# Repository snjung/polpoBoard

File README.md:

# polpoBoard

## Introduction
This repository compiles code and documentation for an electronic scoreboard. It has been successfully operated for several years and was continuously updated and improved.
The idea and inspiration comes from the awesome folks from Westbury on Severn Cricket Club
You can find their blog with tons of useful information on the project at https://buildyourownscoreboard.wordpress.com/

The main idea is to have a Raspberry Pi acting as a web-server and providing control of the scoreboard via a simple webpage to connected devices. The Raspberry Pi will transmit the data to be shown on the scoreboard to an arduino board via serial interface. The Arduino will then control the hardware. Currently this includes
- Custom Build 7-segment elements to show goals and time left of the current game
- A 12V car horn used for signaling end of game / half-time
- Display-Panels build of 8x8 dot-matrix LED elements to show the names of the teams

### Hardware

#### 7-Segment Elements

The 7-Segment elements are custom build and consist of 12V-LED stripes or bars. 

### Control Scheme

To control the high number of LED elements by a single microcontroller (4 x 2digits x 7 LED elements), the schematics uses shift registers for multiplexing.
Some great explanation of the functionality for a shift register can be found at https://www.mikrocontroller.net/articles/AVR-Tutorial:_Schieberegister
Each shift register provides 8 output channels and can be used to control one individual digit of the scoreboard. All shift registers can be cascaded (serial_out connected to serial_in of the next IC) and controlled via one single data pin.
The electrical signals we need are:
- **Serial Data**: Sequence of bit-values indicating if a specific output channel should be enabled/disabled. Due to the shifting, the first bit send to the shift registers will end up to be the last channel of the last register in the chain.
- **Clock signal**, that is in sync with the data signal. On each positive flank, the current value on the serial-data line will be stored in the 1st bit of an internal register of the IC (shift register) and already stored values will be shifted to the next address. Data, that was stored at the last position in the shift register will be send to serial_out / the next shift register IC). Depending on the specific IC, the PIN is usually called SCK or SRCK.
- **Release signal**. When all data has been transmitted thus the internal shift registers of the ICs have been properly set, a rising flank of this signal will cause the current values of the shift register to be transfered to the output register. Only then will the outputs of the ICs actually change state. The corresponding Pin is usually called RCK.
There are some additional signals, that are not essential but could be used for further control of the ICs:
- **Output activation signal** (Usually diaignated G). Can be used to enable/disable the outputs indipendent of the state of the output register. For the relevant ICs, 0V indicates outputs enabled. Therefore, if this function is not required, the corresponding pin can be wired to GND
- **Clear signal**: Can be used to erase all data from the shift register (Setting all bits to 0). If this function is not required, the corresponding pin can be wired to +5V. Default designator for the pin is SCL

For controling the shift registers, we can use the SPI-bus of the Arduino, since it already comes with a resource-efficient implementation for sending serial data with a synchronous clock signal. 
SPI is a three wire communication bus that is intended to connect a number of slave devices to one master device in parallel. The electrical signals are:
- SLK (or SCK / SCLK): Clock signal for synchronising Master and Slave - In our case this corresponds to SCK/SRCK of the shift registers
- MOSI (Master output Slave input) (also called PICO): Used to send data from the Master to the slave - In our case this corresponds to the Serial Data send to the input of the first shift register
- MISO (Master input Slave Output) (also called POCI): Used to send data back to the master - In our case not required

Since all slave devices are connected to the SPI bus in parallel, there must be a mechanism to identify the device that is selected for communication. For this purpose, the SPI-bus uses an additional signal / wire for each slave device, that enables communcication. This pin usually is designated as SS (slave select). The default state of the SS-lines is +5V. During communication with one individual slave, its SS-line will be pulled to GND (for the duration of the communication).

The Shift registers have no slave select pin. However, it is still possible to use these devices in parallel with outher SPI devices by using the RCK pin (Release signal). Although the ICs will process all data (also data meant for other SPI-devices on the bus) and change the internal shift registers accordingly, there won't be any unintended change to the storage register and output channels without setting the RCK-signal. Since the Transfer from shift- to output registers is triggered by a positive flank on the RCK-line, the SS-select signal can be used and directly being hooked to the RCK pin. One should be aware, that when using multiple devices on the SPI-bus, the state of the shift registers might have some arbitrary state after some time. Before enabling the release signal, one must always (re-)set the shift-registers to its correct/intended state.

### Hardware

A convenient choice is the TPIC6B595N. The advantage is, that its open-drain DMOS transistors are intended for high current operation and can directly drive the LED-elements.  With 8 outputs, one TPIC6B595N can provide current to all elements of one 7-segment display. The TPIC6B595N has a continuous sink-current capability of 150mA on each output channel.

If the LED-stripes to be used would sink more than 150mA () the TPIC6B595N would have to be reduced. I could not find suitable devices, that combine the shifter funtionality with the high current output capability. It would probably be advisable to use a dedicated (low current) shifter like a 74HC595 in combination with a multi-channel transistor IC like the ULN2803A. The ULN2803A is capable of sinking 500mA continuously.   

### Software

#### Arduino Softwa

#### Serial Communication

Raspberry Pi and Arduino have to exchange information on the scoreboard status via serial port. The Arduino Firmware uses  CmdMessenger by Thijs Elenbaas to implement the serial communication. Project repository can be found at https://github.com/thijse/Arduino-CmdMessenger. CmdMessengers message format:

``Cmd Id, param 1, [...] , param N;``

Default field seperator is a comma, default command sepeartor is semi-colon.
For our application, the seperators are changed to:
- field seperator: ,
- command seperator: #

There is a Python client to communicate with an Arduino implementing this protocol: https://github.com/harmsm/PyCmdMessenger

#### Control of 7-segment elements

For controlling the 7-segment displays via the TPIC6B595N, the communication and control of the shift register has to be done via SPI. The specific control scheme to control the drain-outputs of the shift registers is implemented in a simple library called polposhifter. This library uses the standard SPI-library that is pre-installed with arduino IDE.

#### Raspberry Pi

For setting-up the Raspberry Pi one can closely followed along the instructions from https://buildyourownscoreboard.wordpress.com/setting-up-the-raspberry-jessie/
The instructions are based on Raspeerry OS 8 (Jessie) and php versiion 5. I used more up-to-date software versions, which works with minimal modification to the. The main steps are:
- Download and install the Raspberry imager from  https://www.raspberrypi.com/software/
- Use this tool to prepare the micro-SD card for the Raspberry (I use a Rev 3 B+ ) with Raspberry Pi OS in lite version (without desktop environement). The Version proposed and used by the installer was bullseye (version 11)
- All further steps can be followed from the linked instructions, with some minor adjustements:
  - When doing the configuration modifications (sudo raspi-config), the mentioned options to be changed are not part of advanced options but instad can be found unter inderface options. When deactivation the serial console I1 lets you activate SSH remote command line access. I6 lets you disable shell and kernel messages on the serial connection. It also asks you, if serial port hardware should be deactivated (choose no) 
  - Installing more recent php-version is straight forward. Just use sudo apt-get install php (instead of php5) and libapache2-mod-phpxxx with the specific php-version that apt-get got tfromit's repositories.
  
  The main operation principle is as follows:
  - The Raspberry hosts an apache webserver, delivering an interactive webpage to connected clients (PC, tablet or smartphone). This has the required interface elements to control the scorepoard and GUI elements to show its current status.
  - The Apache Server runs with enhanced rights (AllowOverride set to All, apache user www-data has user rights to dialout / access serial interface)
  - The web-interface uses javascript routines to implement the scoreboards logic. In essence, all logic is implemented on this level, the arduino is just getting information via serial port on the content, that should be shown on the physical scoreboard. The logic specific javascript-code is part of scoreboard.js.

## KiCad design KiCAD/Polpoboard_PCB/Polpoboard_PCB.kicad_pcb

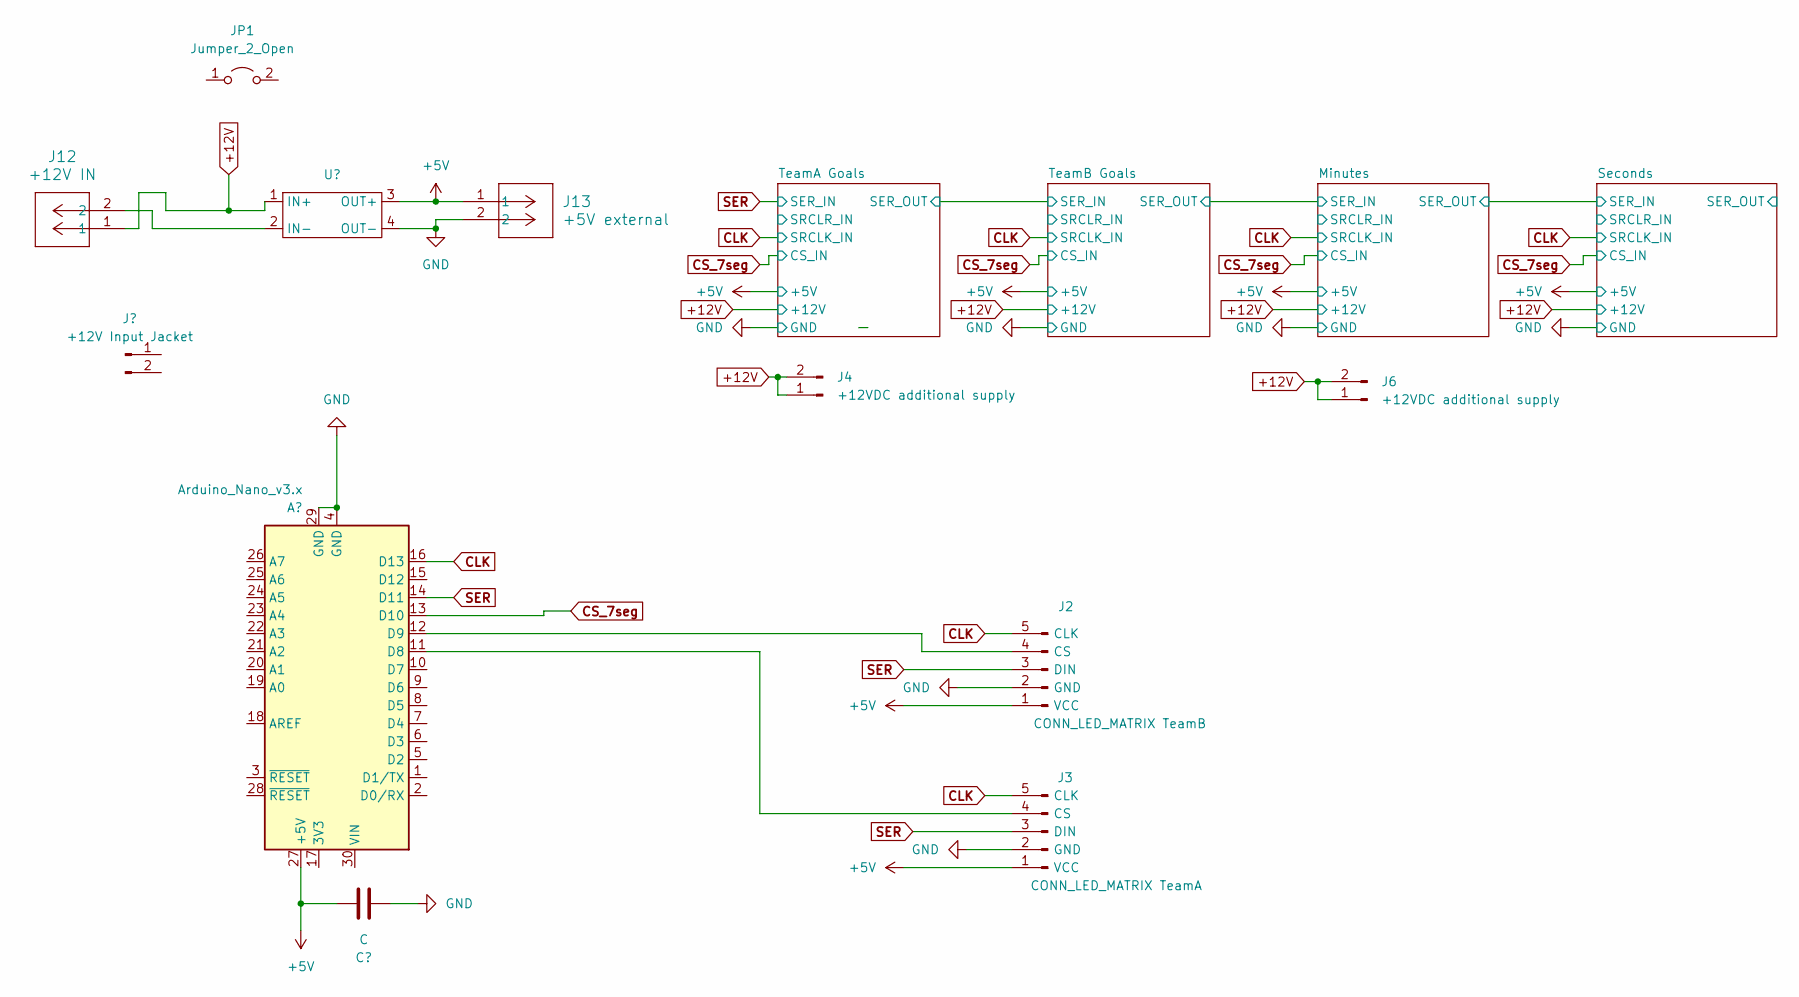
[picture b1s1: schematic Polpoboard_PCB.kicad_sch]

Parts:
A1: Arduino_Nano_v3.x; Arduino_Nano
C1: C; CP_Radial_D6.3mm_P2.50mm
J1: +12V Input Jacket
J2: CONN_LED_MATRIX TeamB; JST_XH_B5B-XH-AM_1x05_P2.50mm_Vertical
J3: CONN_LED_MATRIX TeamA; JST_XH_B5B-XH-AM_1x05_P2.50mm_Vertical
J4, J6: +12VDC additional supply; TerminalBlock_Altech_AK300-2_P5.00mm
J12: +12V IN; CONN2_710002_WRE
J13: +5V external; CONN2_710002_WRE
JP1: Jumper_2_Open
U1: XL4005_DC-DC

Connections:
+5V: A1.27 (+5V), C1.2, J2.1 (VCC), J3.1 (VCC), J13.1, U1.3 (OUT+); also elsewhere on the board
+12V: J4.1, J4.2, J6.1, J6.2, J12.1, U1.1 (IN+); also elsewhere on the board
CLK: A1.16 (D13), J2.5 (CLK), J3.5 (CLK); also elsewhere on the board
CS_7seg: A1.13 (D10); also elsewhere on the board
GND: A1.4 (GND), A1.29 (GND), C1.1, J2.2 (GND), J3.2 (GND), J13.2, U1.4 (OUT-); also elsewhere on the board
unnamed: A1.11 (D8), J3.4 (CS)
unnamed: A1.12 (D9), J2.4 (CS)
unnamed: J12.2, U1.2 (IN-)
SER: A1.14 (D11), J2.3 (DIN), J3.3 (DIN); also elsewhere on the board

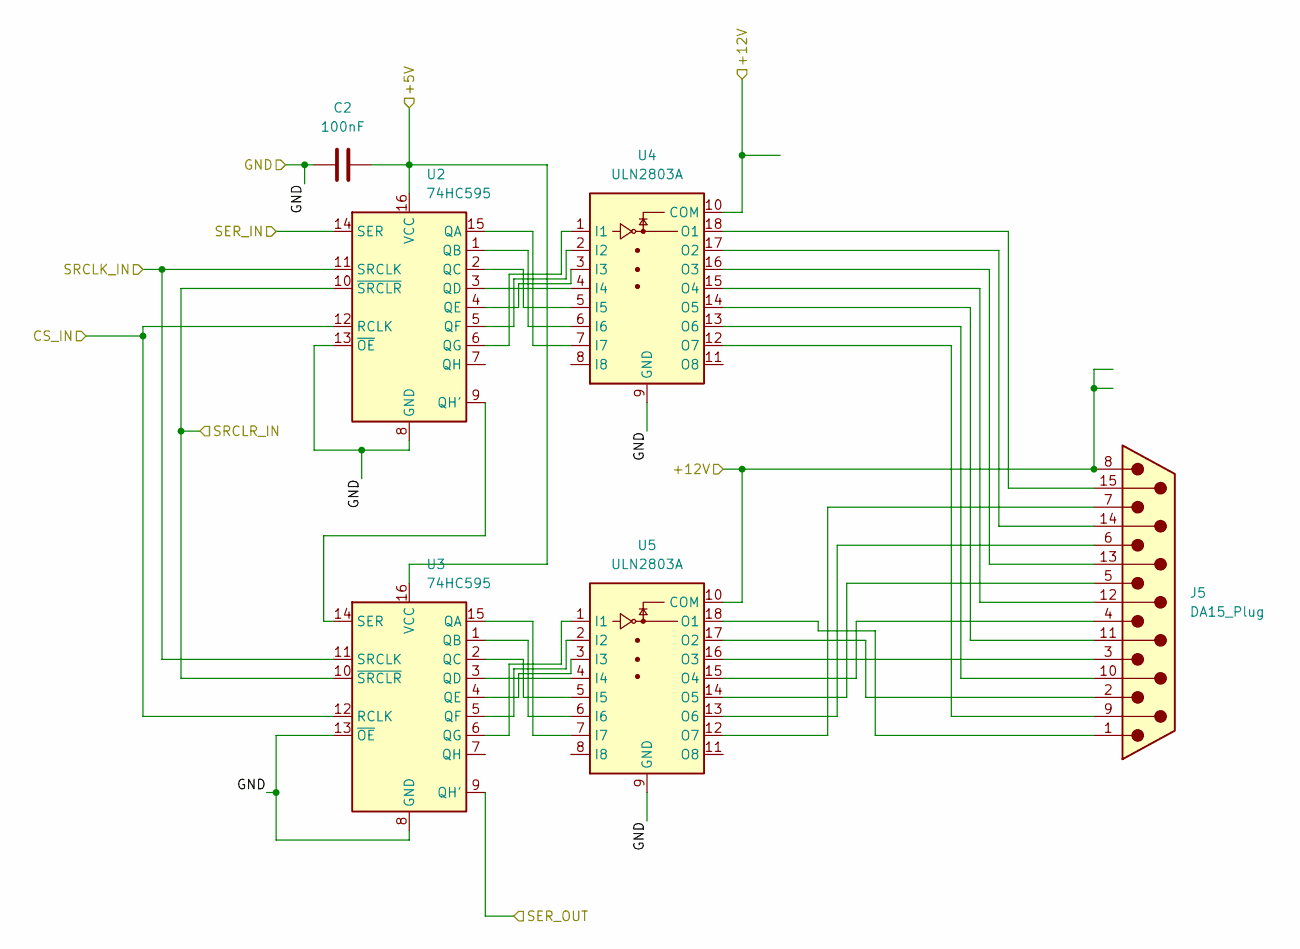
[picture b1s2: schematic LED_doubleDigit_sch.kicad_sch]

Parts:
C2: 100nF; C_Disc_D4.7mm_W2.5mm_P5.00mm
J5: DA15_Plug; DSUB-15
U2, U3: 74HC595; 74HC595N
U4, U5: ULN2803A

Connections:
+5V: C2.2, U2.16 (VCC), U3.16 (VCC); also elsewhere on the board
+12V: J5.8, U4.10 (COM), U5.10 (COM); also elsewhere on the board
/TeamA Goals/SER_OUT: U3.9 (QH'); also elsewhere on the board
/TeamA Goals/SRCLR_IN: U2.10 (~SRCLR), U3.10 (~SRCLR)
CLK: U2.11 (SRCLK), U3.11 (SRCLK); also elsewhere on the board
CS_7seg: U2.12 (RCLK), U3.12 (RCLK); also elsewhere on the board
GND: C2.1, U2.8 (GND), U2.13 (~OE), U3.8 (GND), U3.13 (~OE), U4.9 (GND), U5.9 (GND); also elsewhere on the board
unnamed: J5.9, U4.12 (O7)
unnamed: J5.10, U4.13 (O6)
unnamed: J5.12, U4.15 (O4)
unnamed: J5.13, U4.16 (O3)
unnamed: J5.14, U4.17 (O2)
unnamed: J5.15, U4.18 (O1)
unnamed: J5.11 (P111), U4.14 (O5)
unnamed: U2.15 (QA), U4.7 (I7)
unnamed: U2.1 (QB), U4.6 (I6)
unnamed: U2.2 (QC), U4.5 (I5)
unnamed: U2.3 (QD), U4.4 (I4)
unnamed: U2.4 (QE), U4.3 (I3)
unnamed: U2.5 (QF), U4.2 (I2)
unnamed: U2.6 (QG), U4.1 (I1)
unnamed: U2.9 (QH'), U3.14 (SER)
unnamed: U3.15 (QA), U5.7 (I7)
unnamed: U3.1 (QB), U5.6 (I6)
unnamed: U3.2 (QC), U5.5 (I5)
unnamed: U3.3 (QD), U5.4 (I4)
unnamed: U3.4 (QE), U5.3 (I3)
unnamed: U3.5 (QF), U5.2 (I2)
unnamed: U3.6 (QG), U5.1 (I1)
unnamed: J5.1, U5.18 (O1)
unnamed: J5.2, U5.17 (O2)
unnamed: J5.3, U5.16 (O3)
unnamed: J5.4, U5.15 (O4)
unnamed: J5.5, U5.14 (O5)
unnamed: J5.6, U5.13 (O6)
unnamed: J5.7, U5.12 (O7)
SER: U2.14 (SER); also elsewhere on the board

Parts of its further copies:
C3, C4, C5: 100nF; C_Disc_D4.7mm_W2.5mm_P5.00mm
J7, J9, J11: DA15_Plug; DSUB-15
U6, U7, U10, U11, U14, U15: 74HC595; 74HC595N
U8, U9, U12, U13, U16, U17: ULN2803A

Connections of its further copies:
+5V: C3.2, C4.2, C5.2, U6.16 (VCC), U7.16 (VCC), U10.16 (VCC), U11.16 (VCC), U14.16 (VCC), U15.16 (VCC); also elsewhere on the board
+12V: J7.8, J9.8, J11.8, U8.10 (COM), U9.10 (COM), U12.10 (COM), U13.10 (COM), U16.10 (COM), U17.10 (COM); also elsewhere on the board
/Minutes/SER_IN: U7.9 (QH'), U10.14 (SER)
/Minutes/SER_OUT: U11.9 (QH'), U14.14 (SER)
/Minutes/SRCLR_IN: U10.10 (~SRCLR), U11.10 (~SRCLR)
/Seconds/SER_OUT: U15.9 (QH')
/Seconds/SRCLR_IN: U14.10 (~SRCLR), U15.10 (~SRCLR)
/TeamA Goals/SER_OUT: U6.14 (SER); also elsewhere on the board
/TeamB Goals/SRCLR_IN: U6.10 (~SRCLR), U7.10 (~SRCLR)
CLK: U6.11 (SRCLK), U7.11 (SRCLK), U10.11 (SRCLK), U11.11 (SRCLK), U14.11 (SRCLK), U15.11 (SRCLK); also elsewhere on the board
CS_7seg: U6.12 (RCLK), U7.12 (RCLK), U10.12 (RCLK), U11.12 (RCLK), U14.12 (RCLK), U15.12 (RCLK); also elsewhere on the board
GND: C3.1, C4.1, C5.1, U6.8 (GND), U6.13 (~OE), U7.8 (GND), U7.13 (~OE), U8.9 (GND), U9.9 (GND), U10.8 (GND), U10.13 (~OE), U11.8 (GND), U11.13 (~OE), U12.9 (GND), U13.9 (GND), U14.8 (GND), U14.13 (~OE), U15.8 (GND), U15.13 (~OE), U16.9 (GND), U17.9 (GND); also elsewhere on the board
unnamed: J7.9, U8.12 (O7)
unnamed: J7.10, U8.13 (O6)
unnamed: J7.12, U8.15 (O4)
unnamed: J7.13, U8.16 (O3)
unnamed: J7.14, U8.17 (O2)
unnamed: J7.15, U8.18 (O1)
unnamed: J7.11 (P111), U8.14 (O5)
unnamed: J9.9, U12.12 (O7)
unnamed: J9.10, U12.13 (O6)
unnamed: J9.12, U12.15 (O4)
unnamed: J9.13, U12.16 (O3)
unnamed: J9.14, U12.17 (O2)
unnamed: J9.15, U12.18 (O1)
unnamed: J9.11 (P111), U12.14 (O5)
unnamed: J11.9, U16.12 (O7)
unnamed: J11.10, U16.13 (O6)
unnamed: J11.12, U16.15 (O4)
unnamed: J11.13, U16.16 (O3)
unnamed: J11.14, U16.17 (O2)
unnamed: J11.15, U16.18 (O1)
unnamed: J11.11 (P111), U16.14 (O5)
unnamed: U6.15 (QA), U8.7 (I7)
unnamed: U6.1 (QB), U8.6 (I6)
unnamed: U6.2 (QC), U8.5 (I5)
unnamed: U6.3 (QD), U8.4 (I4)
unnamed: U6.4 (QE), U8.3 (I3)
unnamed: U6.5 (QF), U8.2 (I2)
unnamed: U6.6 (QG), U8.1 (I1)
unnamed: U6.9 (QH'), U7.14 (SER)
unnamed: U7.15 (QA), U9.7 (I7)
unnamed: U7.1 (QB), U9.6 (I6)
unnamed: U7.2 (QC), U9.5 (I5)
unnamed: U7.3 (QD), U9.4 (I4)
unnamed: U7.4 (QE), U9.3 (I3)
unnamed: U7.5 (QF), U9.2 (I2)
unnamed: U7.6 (QG), U9.1 (I1)
unnamed: J7.1, U9.18 (O1)
unnamed: J7.2, U9.17 (O2)
unnamed: J7.3, U9.16 (O3)
unnamed: J7.4, U9.15 (O4)
unnamed: J7.5, U9.14 (O5)
unnamed: J7.6, U9.13 (O6)
unnamed: J7.7, U9.12 (O7)
unnamed: U10.15 (QA), U12.7 (I7)
unnamed: U10.1 (QB), U12.6 (I6)
unnamed: U10.2 (QC), U12.5 (I5)
unnamed: U10.3 (QD), U12.4 (I4)
unnamed: U10.4 (QE), U12.3 (I3)
unnamed: U10.5 (QF), U12.2 (I2)
unnamed: U10.6 (QG), U12.1 (I1)
unnamed: U10.9 (QH'), U11.14 (SER)
unnamed: U11.15 (QA), U13.7 (I7)
unnamed: U11.1 (QB), U13.6 (I6)
unnamed: U11.2 (QC), U13.5 (I5)
unnamed: U11.3 (QD), U13.4 (I4)
unnamed: U11.4 (QE), U13.3 (I3)
unnamed: U11.5 (QF), U13.2 (I2)
unnamed: U11.6 (QG), U13.1 (I1)
unnamed: J9.1, U13.18 (O1)
unnamed: J9.2, U13.17 (O2)
unnamed: J9.3, U13.16 (O3)
unnamed: J9.4, U13.15 (O4)
unnamed: J9.5, U13.14 (O5)
unnamed: J9.6, U13.13 (O6)
unnamed: J9.7, U13.12 (O7)
unnamed: U14.15 (QA), U16.7 (I7)
unnamed: U14.1 (QB), U16.6 (I6)
unnamed: U14.2 (QC), U16.5 (I5)
unnamed: U14.3 (QD), U16.4 (I4)
unnamed: U14.4 (QE), U16.3 (I3)
unnamed: U14.5 (QF), U16.2 (I2)
unnamed: U14.6 (QG), U16.1 (I1)
unnamed: U14.9 (QH'), U15.14 (SER)
unnamed: U15.15 (QA), U17.7 (I7)
unnamed: U15.1 (QB), U17.6 (I6)
unnamed: U15.2 (QC), U17.5 (I5)
unnamed: U15.3 (QD), U17.4 (I4)
unnamed: U15.4 (QE), U17.3 (I3)
unnamed: U15.5 (QF), U17.2 (I2)
unnamed: U15.6 (QG), U17.1 (I1)
unnamed: J11.1, U17.18 (O1)
unnamed: J11.2, U17.17 (O2)
unnamed: J11.3, U17.16 (O3)
unnamed: J11.4, U17.15 (O4)
unnamed: J11.5, U17.14 (O5)
unnamed: J11.6, U17.13 (O6)
unnamed: J11.7, U17.12 (O7)

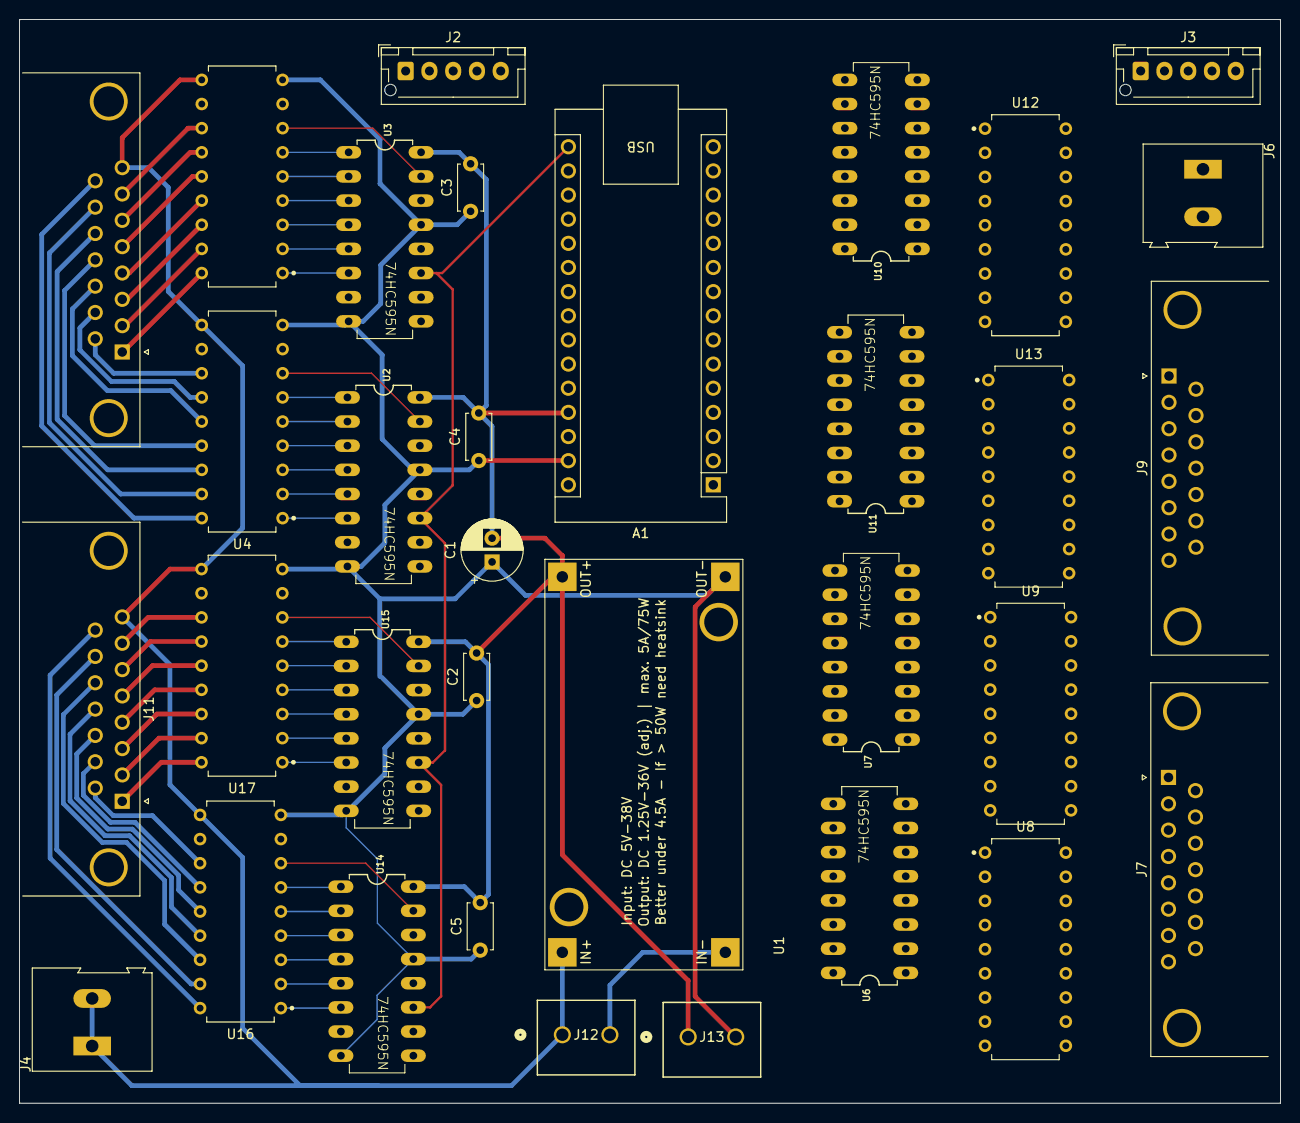
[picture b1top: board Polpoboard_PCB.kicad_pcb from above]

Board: 2 copper layers, 132.6 x 114.0 mm, 33 parts (0 on the bottom side), 132 nets.

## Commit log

2023-12-23 Include pre-existing files to the repsitory
2024-01-19 Update README.md
    Added information on shift registers and SPI-bus
2024-01-20 Collecting all the pieces from prior work
2024-01-22 LED-Matrix with Double Height Initial work on Arduino implementation
2024-01-22 Added batch file to copy arduino files to the default library folder
2024-01-24 Added Arduino test integration for CmdMessenger Latest version of library has changed cmd-set modification required
2024-01-24 Initial work on Arduino Controller PCB
2024-01-25 restrucutred Arduino folder
2024-01-30 Updated version of KiCAD PCB files
2024-02-08 Minor updates to the PCB
